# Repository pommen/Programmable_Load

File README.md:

# Programmable-Load

Programmable DC load 0-10 amps 0-40 volts
Based on STM32 "bluepill" mcu running STMduino core.

All schematics in KiĆAD

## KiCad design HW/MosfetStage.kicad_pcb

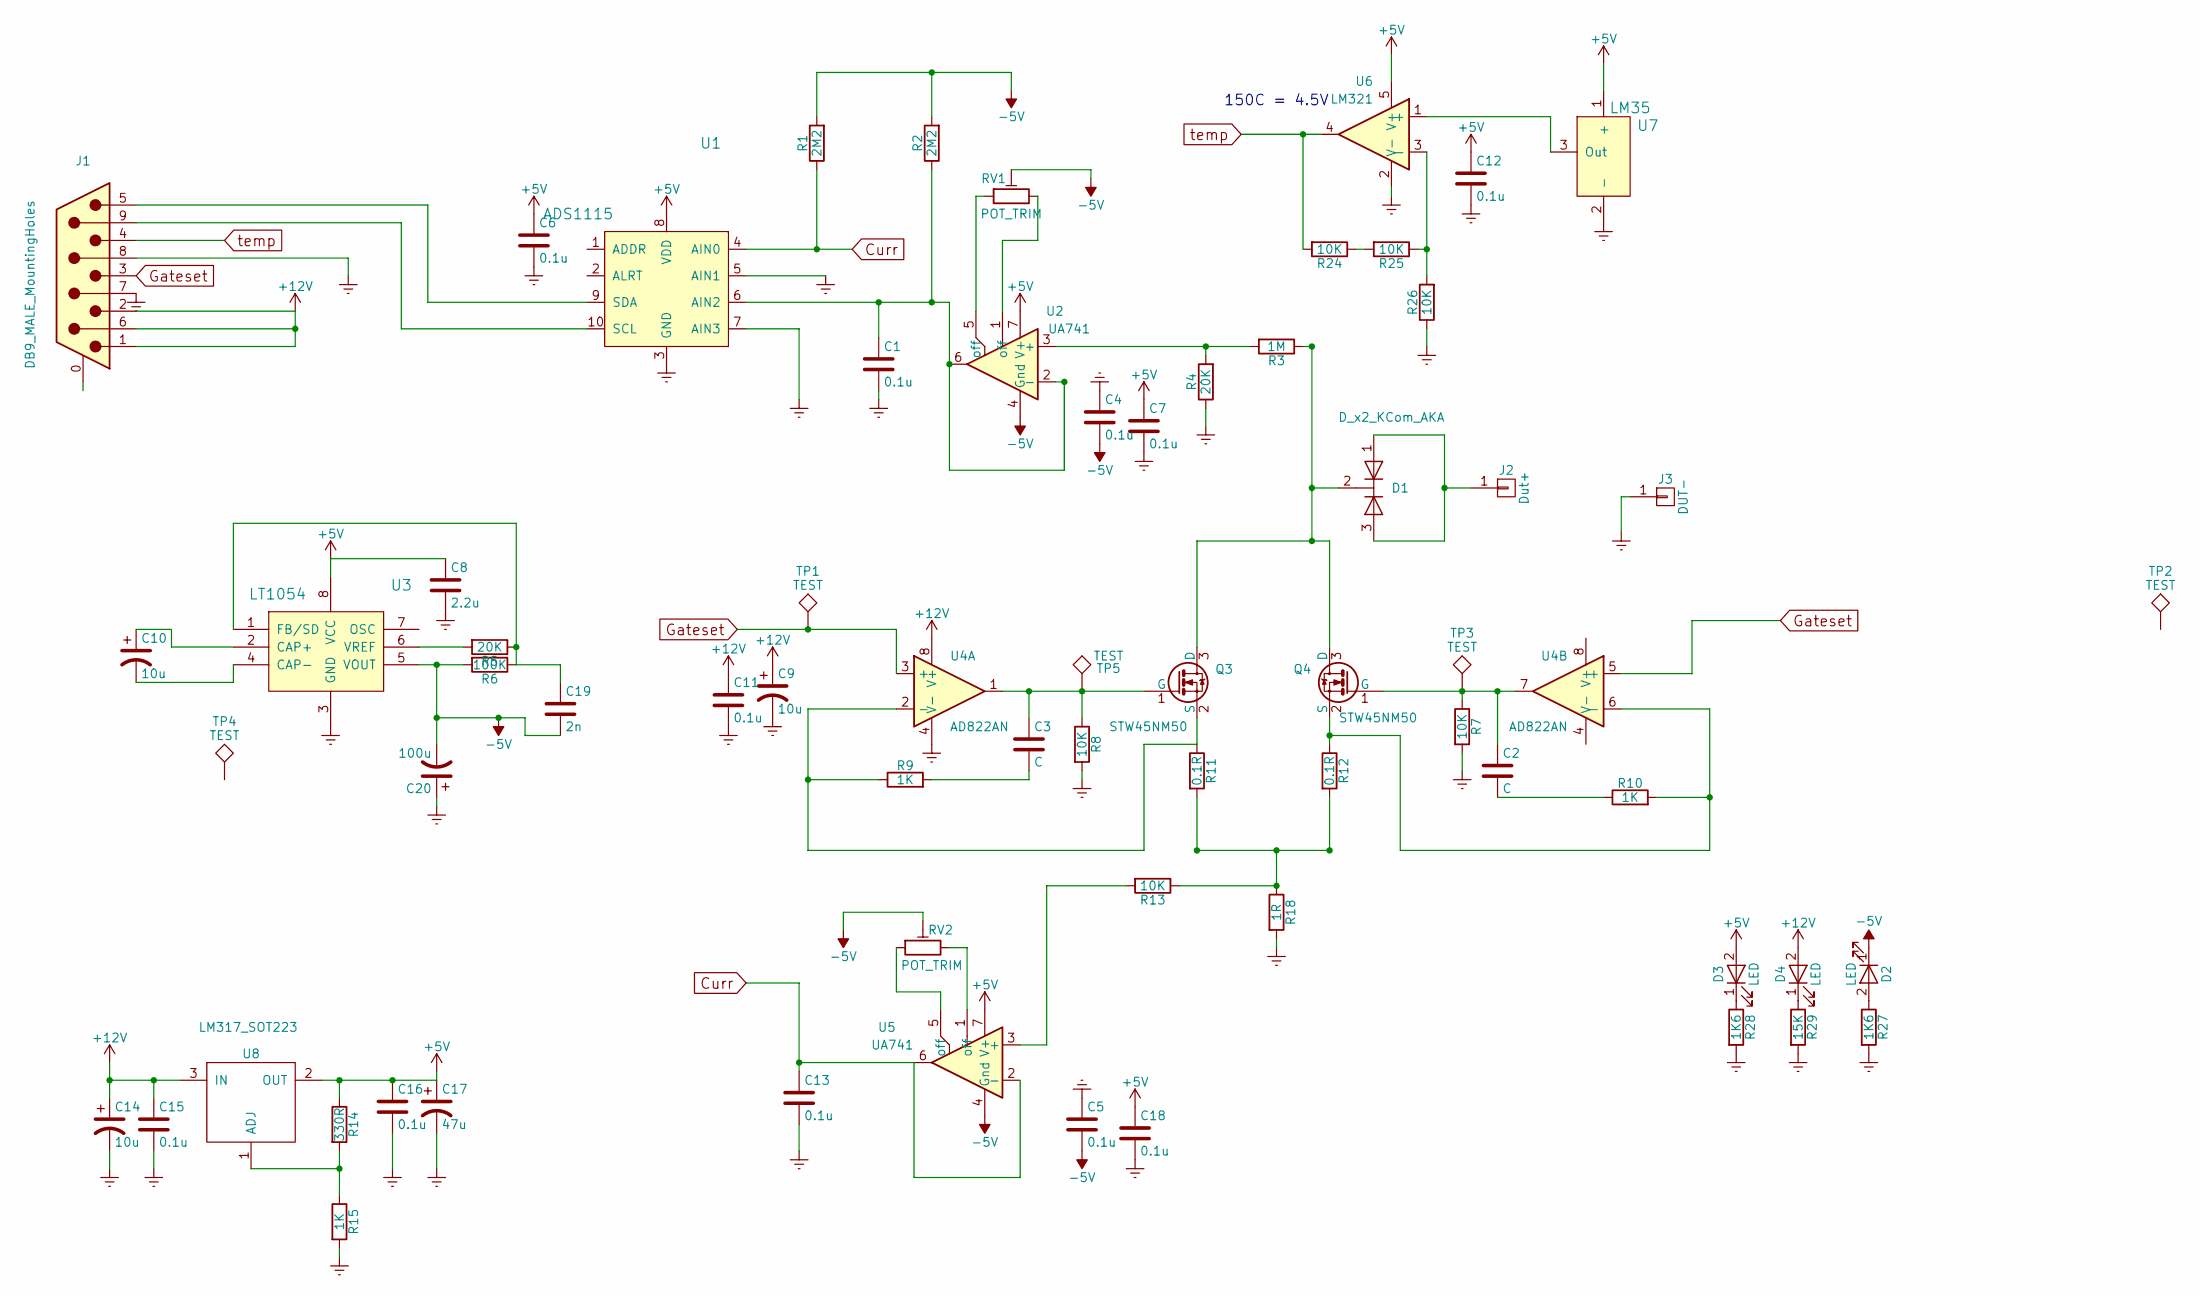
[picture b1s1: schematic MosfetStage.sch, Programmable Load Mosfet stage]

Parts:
C1, C4, C5, C6, C7, C11, C12, C13, C15, C18: 0.1u; C_0805_HandSoldering
C2, C3: C; C_0805_HandSoldering
C8: 2.2u; C_0805_HandSoldering
C9, C10: 10u; CP_Tantalum_Case-B_EIA-3528-21_Hand
C14: 10u; CP_Radial_D8.0mm_P3.50mm
C16: 0.1u; CP_Tantalum_Case-T_EIA-3528-12_Hand
C17: 47u; CP_Tantalum_Case-T_EIA-3528-12_Hand
C19: 2n; C_0805_HandSoldering
C20: 100u; CP_Tantalum_Case-B_EIA-3528-21_Hand
D1: D_x2_KCom_AKA; TO-263-2
D2, D3, D4: LED; LED_0805_HandSoldering
J1: DB9_MALE_MountingHoles; DB9MC
J2: Dut+; MountingHole_3.2mm_M3
J3: DUT-; MountingHole_3.2mm_M3
Q3, Q4: STW45NM50; TO-247_TO-3P_Horizontal
R1, R2: 2M2; R_0805_HandSoldering
R3: 1M; R_0805_HandSoldering
R4, R5: 20K; R_0805_HandSoldering
R6: 100K; R_0805_HandSoldering
R7, R8, R13, R24, R25, R26: 10K; R_0805_HandSoldering
R9, R10, R15: 1K; R_0805_HandSoldering
R11, R12: 0.1R; R_Axial_Power_L25.0mm_W9.0mm_P27.94mm
R14: 330R; R_0805_HandSoldering
R18: 1R; R_Axial_DIN0516_L15.5mm_D5.0mm_P20.32mm_Horizontal
R27, R28: 1K6; R_0805_HandSoldering
R29: 15K; R_0805_HandSoldering
RV1, RV2: POT_TRIM; Potentiometer_Trimmer_ACP_CA9h3.8_Vertical_Px3.8mm_Py5.0mm
TP1, TP2, TP3, TP4, TP5: TEST; Measurement_Point_Round-TH_Big
U1: ADS1115; ADS1115-Breakout
U2, U5: UA741; DIP-8_W7.62mm_Socket_LongPads
U3: LT1054; DIP-8_W7.62mm_LongPads
U4: AD822AN; DIP-8_W7.62mm_LongPads
U6: LM321; SOT-23-5
U7: LM35; TO-220_Vertical
U8: LM317_SOT223; SOT-223

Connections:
+5V: C6.1, C7.1, C8.1, C12.1, C16.1, C17.1, C18.1, D3.2 (A), R14.1, U1.8 (VDD), U2.7 (V+), U3.8 (VCC), U5.7 (V+), U6.5 (V+), U7.1 (+), U8.2 (OUT)
+12V: C9.1, C11.1, C14.1, C15.1, D4.2 (A), J1.1, J1.2, J1.6, U4.8 (V+), U8.3 (IN)
-5V: C4.2, C5.2, C19.2, C20.2, D2.1 (K), R1.2, R2.2, R6.2, RV1.2, RV2.2, U2.4 (Gnd), U3.5 (VOUT), U5.4 (Gnd)
Curr: C13.1, R1.1, U1.4 (AIN0), U5.2 (-), U5.6
Earth: C1.2, C4.1, C5.1, C6.2, C7.2, C8.2, C9.2, C11.2, C12.2, C13.2, C14.2, C15.2, C16.2, C17.2, C18.2, C20.1, J1.7, J1.8, J3.1, R4.1, R7.2, R8.2, R15.2, R18.2, R26.1, R27.2, R28.2, R29.2, U1.3 (GND), U1.5 (AIN1), U1.7 (AIN3), U3.3 (GND), U4.4 (V-), U6.2 (V-), U7.2 (-)
Gateset: J1.3, TP1.1, U4.3 (+), U4.5 (+)
unnamed: C1.1, R2.1, U1.6 (AIN2), U2.2 (-), U2.6
unnamed: C2.1, Q4.1 (G), R7.1, TP3.1, U4.7
unnamed: C2.2, R10.1
unnamed: C3.1, Q3.1 (G), R8.1, TP5.1, U4.1
unnamed: C3.2, R9.2
unnamed: C10.1, U3.2 (CAP+)
unnamed: C10.2, U3.4 (CAP-)
unnamed: C19.1, R5.1, R6.1, U3.1 (FB/SD)
unnamed: D1.1 (A), D1.3 (A), J2.1
unnamed: D1.2 (K), Q3.3 (D), Q4.3 (D), R3.1
unnamed: D2.2 (A), R27.1
unnamed: D3.1 (K), R28.1
unnamed: D4.1 (K), R29.1
unnamed: J1.5, U1.9 (SDA)
unnamed: J1.9, U1.10 (SCL)
unnamed: Q3.2 (S), R9.1, R11.1, U4.2 (-)
unnamed: Q4.2 (S), R10.2, R12.1, U4.6 (-)
unnamed: R3.2, R4.2, U2.3 (+)
unnamed: R5.2, U3.6 (VREF)
unnamed: R11.2, R12.2, R13.1, R18.1
unnamed: R13.2, U5.3 (+)
unnamed: R14.2, R15.1, U8.1 (ADJ)
unnamed: R24.1, R25.2
unnamed: R25.1, R26.2, U6.3 (-)
unnamed: RV1.1, U2.5 (off)
unnamed: RV1.3, U2.1 (off)
unnamed: RV2.1, U5.5 (off)
unnamed: RV2.3, U5.1 (off)
unnamed: U6.1 (+), U7.3 (Out)
temp: J1.4, R24.2, U6.4

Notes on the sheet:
150C = 4.5V

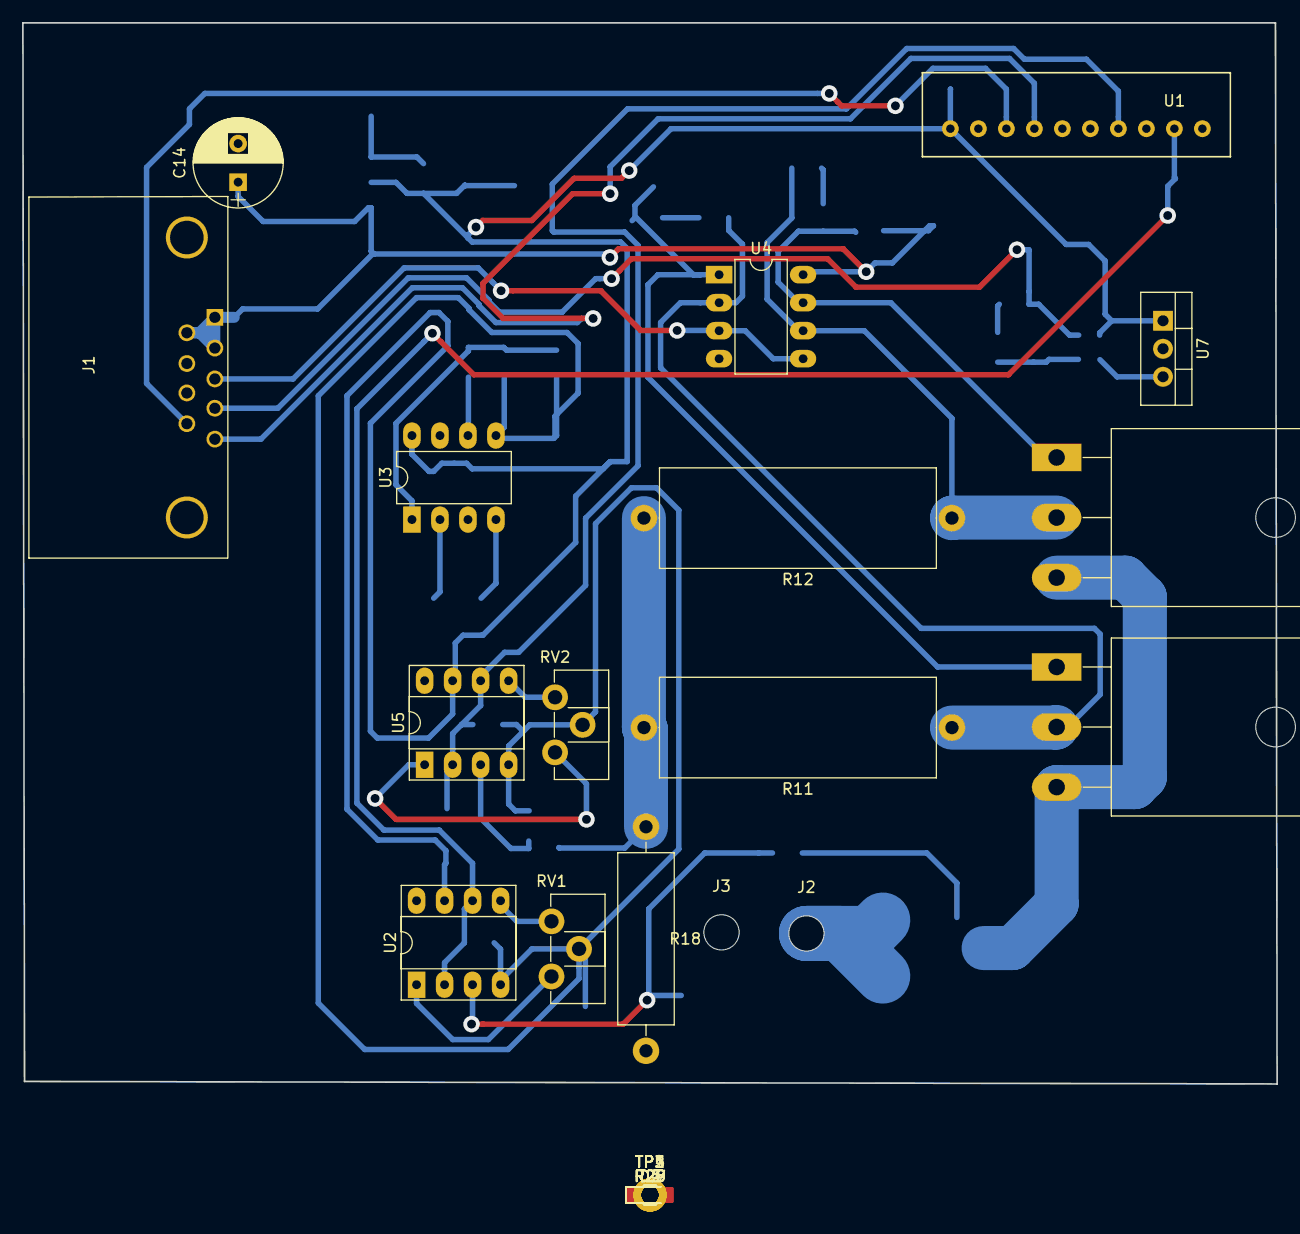
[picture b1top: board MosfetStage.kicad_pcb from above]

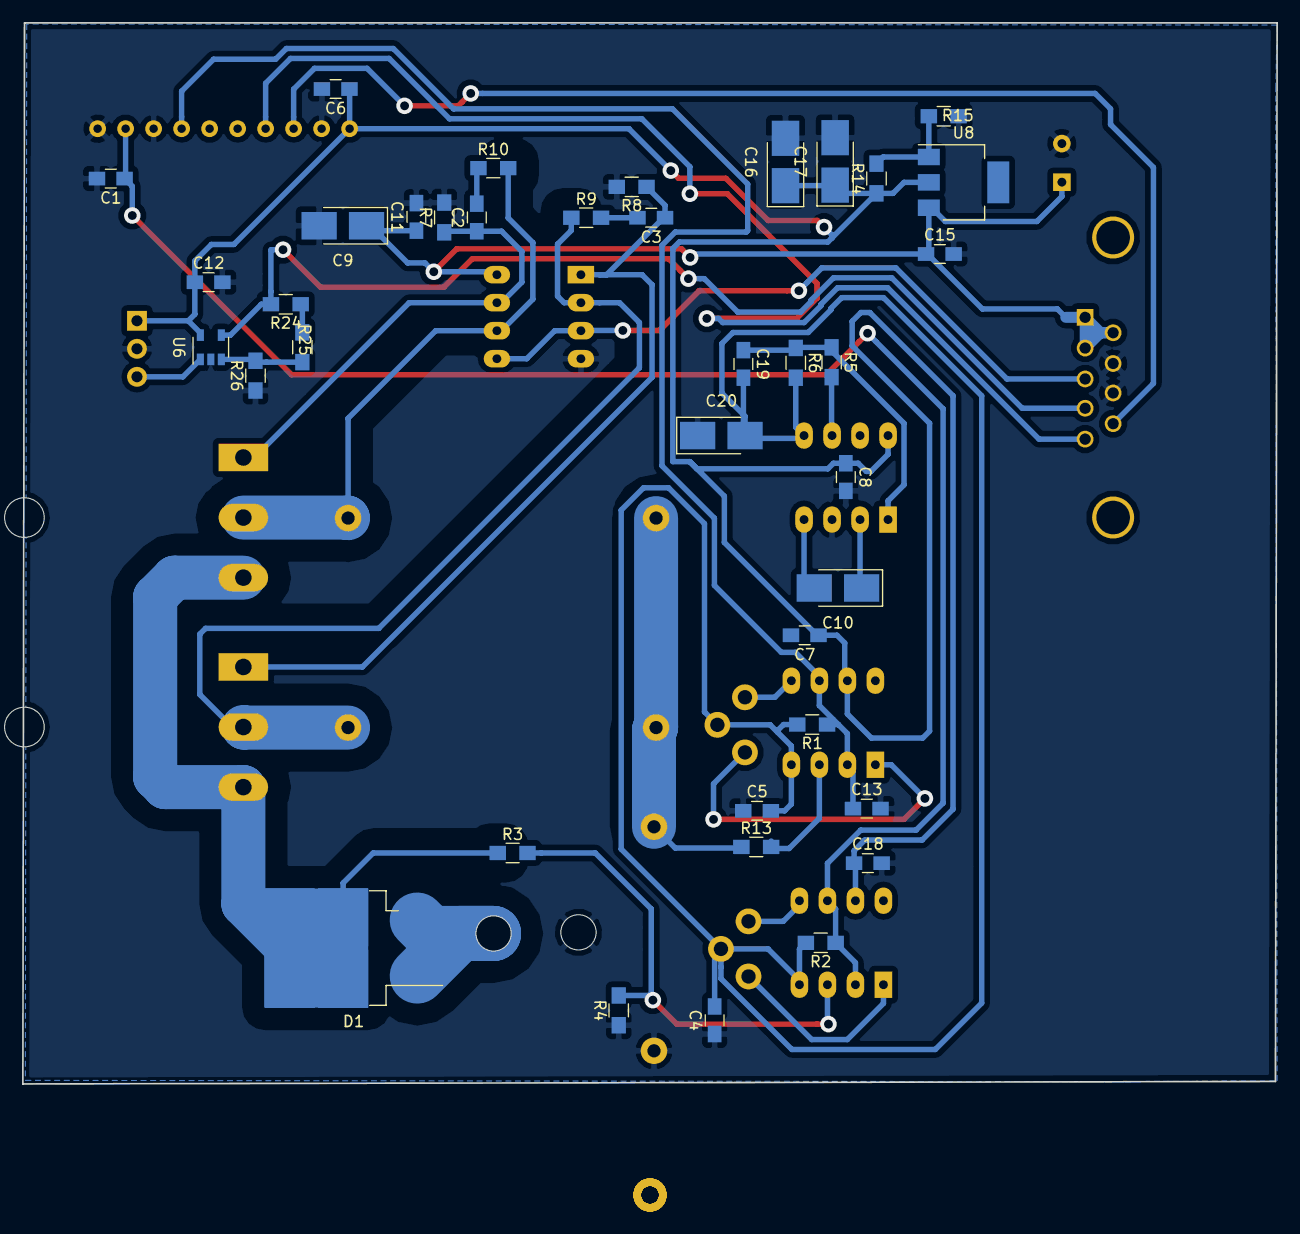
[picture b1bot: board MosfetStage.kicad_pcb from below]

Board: 2 copper layers, 113.8 x 96.2 mm, 66 parts (38 on the bottom side), 36 nets.

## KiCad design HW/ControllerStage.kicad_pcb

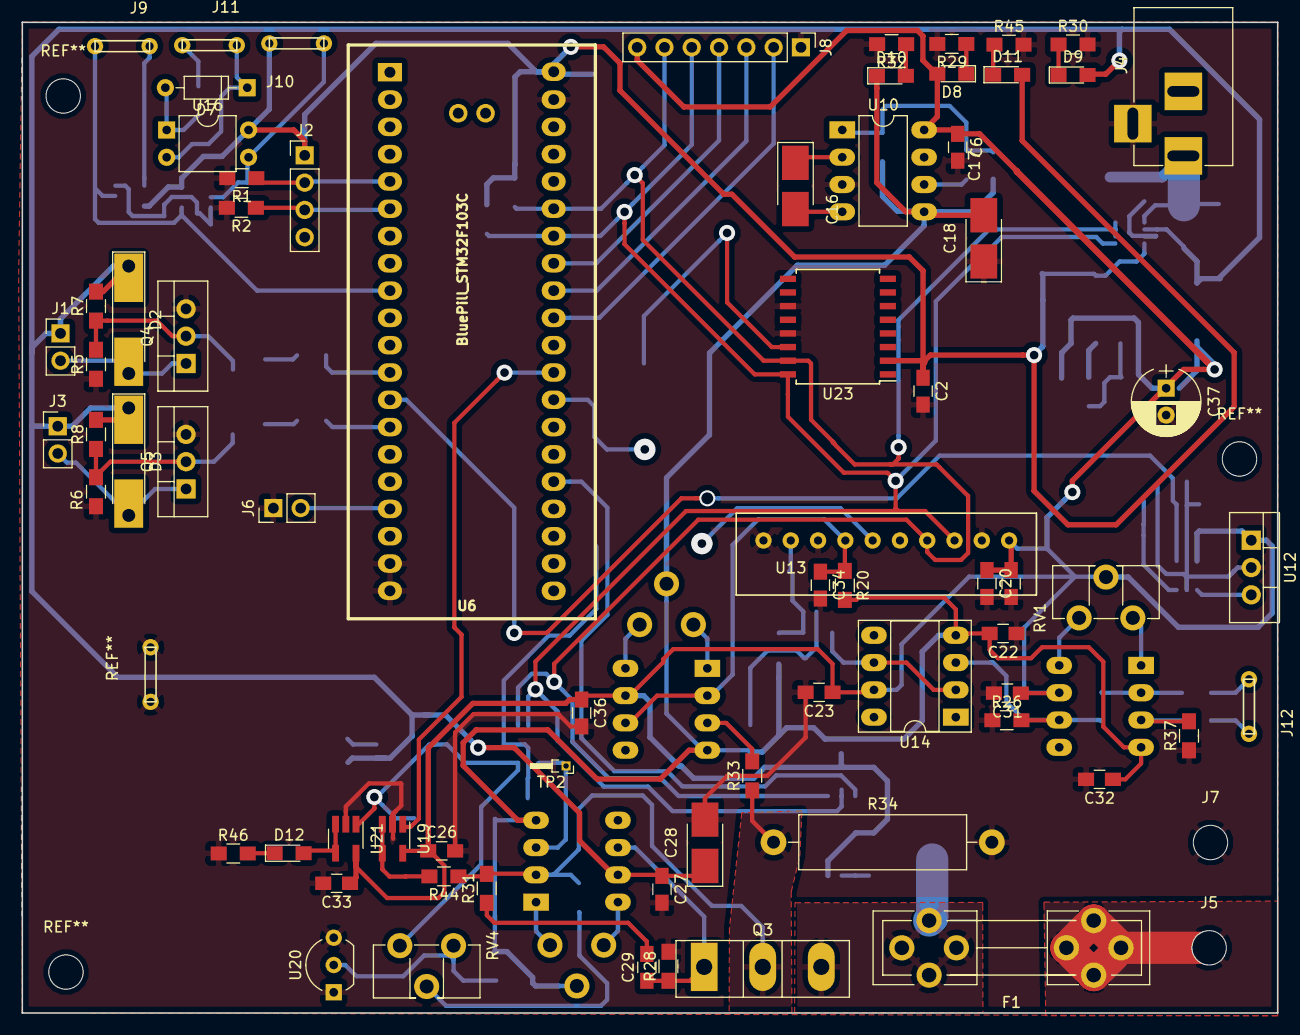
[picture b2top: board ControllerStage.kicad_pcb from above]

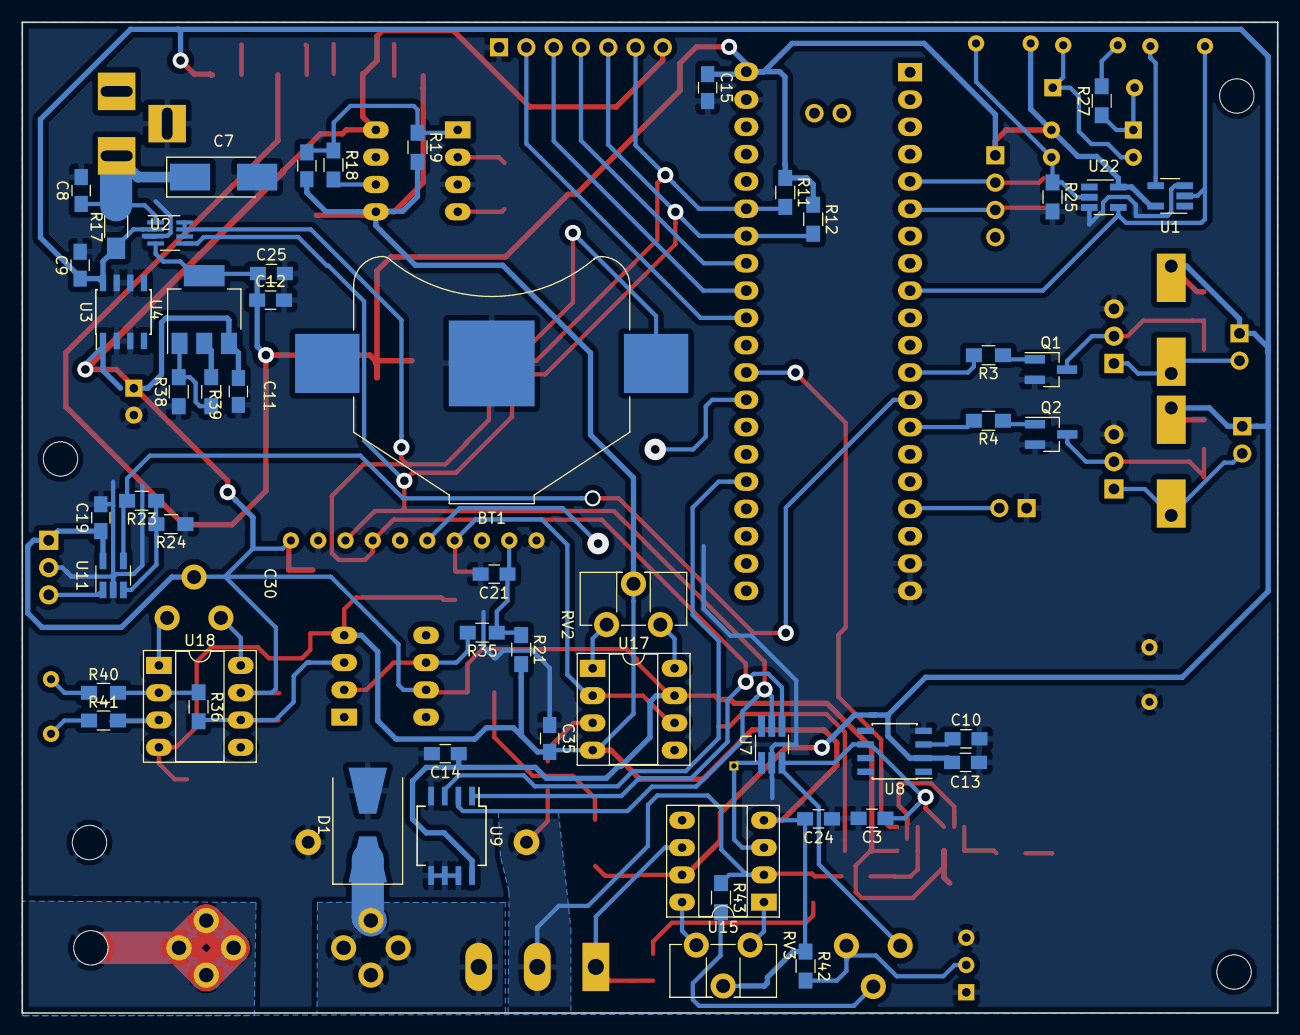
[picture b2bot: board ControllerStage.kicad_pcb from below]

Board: 2 copper layers, 116.8 x 92.2 mm, 128 parts (54 on the bottom side), 72 nets.

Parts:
BT1: Battery_Cell; Keystone_3008_1x2450-CoinCell
C2, C15, C25, C33: 100n; C_0805_HandSoldering
C3, C9: 100nF; C_0805_HandSoldering
C6: 2.2u; C_0805_HandSoldering
C7: CP1_Small; CP_Tantalum_Case-C_EIA-6032-28_Hand
C8, C11, C12: C_Small; C_0805_HandSoldering
C10: 1uF; C_0805_HandSoldering
C13: 2.2uF; C_0805_HandSoldering
C14: 0,1u; C_0805_HandSoldering
C16, C28: 10u; CP_Tantalum_Case-B_EIA-3528-21_Hand
C17: 2n; C_0805_HandSoldering
C18: 100u; CP_Tantalum_Case-B_EIA-3528-21_Hand
C19, C20, C21, C22, C23, C24, C26, C27, C34, C35, C36: 0.1u; C_0805_HandSoldering
C29: 1n; C_0805_HandSoldering
C30: 10u; C_0805_HandSoldering
C31, C32: C; C_0805_HandSoldering
C37: 100uF; CP_Radial_D6.3mm_P2.50mm
D1: D_Schottky; D_SMB-SMC_Universal_Handsoldering
D2, D3: D_ALT; D_MELF-RM10_Universal_Handsoldering
D7: 1N4148; D_DO-35_SOD27_P7.62mm_Horizontal
D8, D9, D10, D11, D12: LED; LED_0805_HandSoldering
F1: Fuse; Fuseholder5x20_horiz_open_universal_Type-III
J1, J3: Load_relay; Socket_Strip_Straight_1x02_Pitch2.54mm
J2: Mosfet_temp; Socket_Strip_Straight_1x04_Pitch2.54mm
J4: BARREL_JACK
J5: Dut+; MountingHole_3.2mm_M3
J6: reset; Pin_Header_Straight_1x02_Pitch2.54mm
J7: DUT-; MountingHole_3.2mm_M3
J8: Encoder and LCD interface; Pin_Header_Straight_1x07_Pitch2.54mm
J9: ScopeTest; JUMPER_5MM
J10: Trigger BTN; JUMPER_5MM
J11: External trigger; JUMPER_5MM
J12: Remote_sense; JUMPER_5MM
Q1, Q2: BC847; SOT-23_Handsoldering
Q3: STW45NM50; TO-247_TO-3P_Vertical
Q4, Q5: BUZ11; TO-220-3_Vertical
R1, R2, R7, R8, R24, R26, R28, R33: 10K; R_0805_HandSoldering
R3, R4, R27, R35: 100R; R_0805_HandSoldering
R5, R6, R19: 100K; R_0805_HandSoldering
R11, R12, R31: 1K; R_0805_HandSoldering
R17: 0R1; R_1206_HandSoldering
R18, R23, R36, R37: 20K; R_0805_HandSoldering
R20: 2M2; R_0805_HandSoldering
R21: 270K; R_0805_HandSoldering
R25, R42: R; R_0805_HandSoldering
R29, R32, R45, R46: 1K6; R_0805_HandSoldering
R30: 15K; R_0805_HandSoldering
R34: 0.1; R_Axial_DIN0516_L15.5mm_D5.0mm_P20.32mm_Horizontal
R38: 390; R_0805_HandSoldering
R39: 240; R_0805_HandSoldering
R40, R41: 1M; R_0805_HandSoldering
R43, R44: 4M7; R_0805_HandSoldering
RV1, RV2, RV3: POT_TRIM; Potentiometer_Trimmer_ACP_CA9h3.8_Vertical_Px3.8mm_Py5.0mm
RV4: Null cal; Potentiometer_Trimmer_ACP_CA9h3.8_Vertical_Px3.8mm_Py5.0mm
TP2: TEST; Pin_Header_Angled_1x01_Pitch1.00mm
U1, U22: SN74LVC1G14; SOT-23-5_HandSoldering
U2: INA219; SOT-23-8_Handsoldering
U3: lm2931-5.0; SOIC-8_3.9x4.9mm_Pitch1.27mm
U4: LM317_3PinPackage; SOT-223-3_TabPin2
U6: BluePill_STM32F103C
U7: MCP4725; TSOT-23-6_HandSoldering
U8: MAX6241; SOIC-8_3.9x4.9mm_Pitch1.27mm
U9: LM75; SO-8_5.3x6.2mm_Pitch1.27mm
U10: LT1054; DIP-8_W7.62mm_LongPads
U11, U19, U21: LM321; SOT-23-5_HandSoldering
U12: LM35; TO-220-3_Vertical
U13: ADS1115; ADS1115-Breakout
U14, U15, U17, U18: OP07; DIP-8_W7.62mm_Socket_LongPads
U16: PC817; DIP-4_W7.62mm
U20: TL431A; TO-92_Inline_Wide
U23: DS3231; SOIC-16W_7.5x10.3mm_Pitch1.27mm

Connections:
4.096V: C3.1, RV4.3, U7.3, U8.6, U21.1
+3V3: C2.1, C12.1, C15.1, C25.1, D11.2, J2.1, J10.2, R11.1, R12.1, R39.2, U1.5, U2.4, U4.2, U6.18, U6.40, U16.4, U22.5, U23.2
+5V: C6.1, C11.1, C14.1, C19.1, C20.1, C23.1, C26.1, C30.1, C31.1, C33.1, C36.1, C37.1, D8.2, J8.7, RV1.2, U3.1, U4.3, U9.8, U10.8, U11.5, U12.1, U13.8, U14.7, U17.7, U18.7, U19.5, U21.5
+12V: C9.1, C13.1, C27.1, C28.1, D2.1, D3.1, D9.2, J1.1, J3.1, R7.2, R8.2, R17.1, U2.2, U3.8, U8.2, U15.7
-5V: C17.2, C18.2, C22.2, C24.2, C32.1, C35.2, D10.1, R19.2, R20.2, R21.2, R42.1, RV2.2, RV3.2, U10.5, U14.4, U15.4, U17.4, U18.4
/Mosfet stage/Dut+_efter_säkring: F1.1, J5.1
Curr: C34.1, R20.1, U13.4, U17.2, U17.6
CurrentSet: TP2.1, U7.1, U15.3
Earth: BT1.2, C2.2, C3.2, C6.2, C7.2, C8.2, C9.2, C10.2, C11.2, C12.2, C13.2, C14.2, C15.2, C18.1, C19.2, C20.2, C21.2, C22.1, C23.2, C24.1, C25.2, C26.2, C27.2, C28.2, C30.2, C31.2, C32.2, C33.2, C34.2, C35.1, C36.2, C37.2, D1.2, J4.3, J6.1, J7.1, J8.1, Q1.2, Q2.2, Q4.3, Q5.3, R1.2, R2.2, R5.1, R6.1, R24.1, R25.2, R26.1, R28.2, R29.2, R30.2, R32.2, R34.2, R37.1, R38.1, R45.2, R46.1, U1.3, U2.3, U3.2, U3.3, U3.6, U3.7, U6.19, U6.20, U6.39, U7.2, U8.4, U9.4, U9.5, U9.6, U9.7, U10.3, U11.2, U12.2, U13.3, U13.5, U13.7, U19.2, U20.1, U20.3, U21.2, U22.3, U23.11, U23.13
LoadBlockTemp: R23.2, U6.13, U11.4
Mosfet1: J2.2, R1.1, U6.5
Mosfet2: J2.3, R2.1, U6.6
unnamed: BT1.1, U23.14
unnamed: C7.1, C8.1, J4.1, R17.2, U2.1
unnamed: C10.1, U8.3
unnamed: C16.1, U10.2
unnamed: C16.2, U10.4
unnamed: C17.1, R18.1, R19.1, U10.1
unnamed: C21.1, R21.1, R35.1, U13.6
unnamed: C29.1, Q3.1, R28.1, U15.6
unnamed: C29.2, R31.1
unnamed: D1.1, F1.2, Q3.3
unnamed: D2.2, J1.2, Q4.1
unnamed: D3.2, J3.2, Q5.1
unnamed: D7.1, J11.2, U16.2
unnamed: D7.2, R27.1, U16.1
unnamed: D8.1, R29.1
unnamed: D9.1, R30.1
unnamed: D10.2, R32.1
unnamed: D11.1, R45.1
unnamed: D12.1, R46.2
unnamed: D12.2, U21.3, U21.4
unnamed: J6.2, U6.17
unnamed: J9.2, U1.4
unnamed: J10.1, R25.1, U16.3, U22.2
unnamed: J11.1, R27.2
unnamed: J12.1, R40.1
unnamed: J12.2, R41.1
unnamed: Q1.1, R3.1
unnamed: Q1.3, Q4.2, R5.2, R7.1
unnamed: Q2.1, R4.1
unnamed: Q2.3, Q5.2, R6.2, R8.1
unnamed: Q3.2, R31.2, R33.1, R34.1, R43.1, R44.1, U15.2
unnamed: R18.2, U10.6
unnamed: R23.1, R24.2, U11.3
unnamed: R26.2, R36.2, U14.3, U18.6
unnamed: R33.2, U17.3
unnamed: R35.2, U14.2, U14.6
unnamed: R36.1, R40.2, U18.2
unnamed: R37.2, R41.2, U18.3
unnamed: R38.2, R39.1, U4.1
unnamed: R42.2, RV4.1, U20.2
unnamed: R43.2, RV4.2
unnamed: R44.2, U19.3, U19.4
unnamed: RV1.1, U18.8
unnamed: RV1.3, U18.1
unnamed: RV2.1, U17.1
unnamed: RV2.3, U17.8
unnamed: RV3.1, U15.1
unnamed: RV3.3, U15.8
unnamed: U11.1, U12.3
OverTemp: U6.25, U9.3
SCL: J8.5, R12.2, U2.5, U6.34, U7.5, U9.2, U13.10, U23.16
SDA: J8.6, R11.2, U2.6, U2.7, U2.8, U6.35, U7.4, U9.1, U13.9, U23.15
comperator: U6.28, U13.2
encA: J8.3, U6.32
encB: J8.2, U6.31
encBTN: J8.4, U6.33
loadOff: U6.29, U19.1
out1: R3.2, U6.12
out2: R4.2, U6.14
trig: J9.1, U1.2, U6.9, U22.4

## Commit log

2017-09-02 Fet drive board
2017-09-10 Sunday tinkering
2017-09-10 Compiles
2017-09-23 Added pwm for fan
2017-09-30 Logic for enable load switch
2017-10-10 Better comments
2017-10-10 Spelling..
2018-04-02 Schematic and layout
2018-04-02 New layout
2018-04-12 running
2018-04-12 accel
2018-04-12 somethingsomething
2018-04-14 so far so good
2018-04-14 fan control and bug fixes
2018-04-15 cleanup
2018-04-15 porting to vscode
2018-04-15 manual trigger and toggle
2018-04-15 söndags
2018-04-19 cleanup - getting ready for v0.2
2018-04-19 V0.2
2018-04-20 layout
2018-04-21 friday layout
2018-04-21 i2c pots for calibrating
2018-04-22 v2 done
2018-04-27 press "b"
2018-05-05 Before starting saturday
2018-05-05 Saturday Coding
2018-05-06 Sunday
2018-05-13 starter manu
2018-05-13 using click libary
2018-05-13 Sunday ca, mneu and buttons
2018-05-13 Frist SW cal draft
2018-05-14 Först SW cal funkar! woohoo
2018-05-15 Voltage cal DONE!
2018-05-17 SW curent cal done
2018-05-19 Friday coding
2018-06-22 soon done
2018-08-19 more
